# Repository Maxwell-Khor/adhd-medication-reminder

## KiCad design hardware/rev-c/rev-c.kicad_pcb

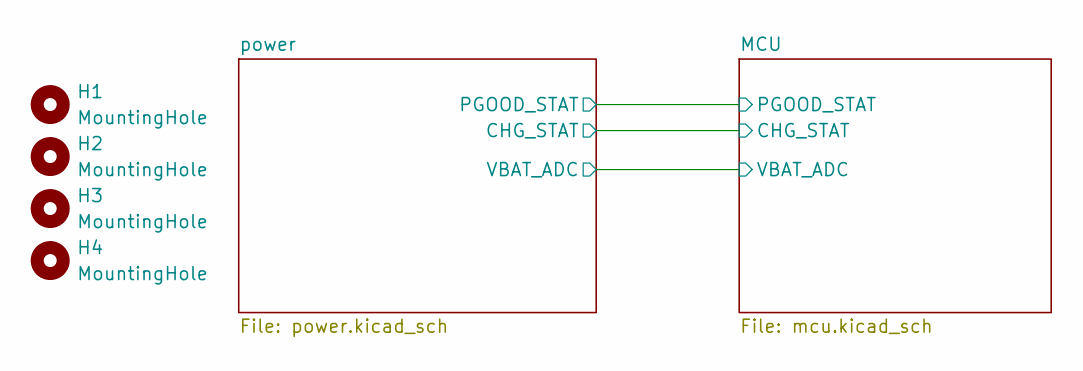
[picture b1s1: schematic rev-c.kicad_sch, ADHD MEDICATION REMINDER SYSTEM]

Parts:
H1, H2, H3, H4: MountingHole; MountingHole_2.2mm_M2_Pad

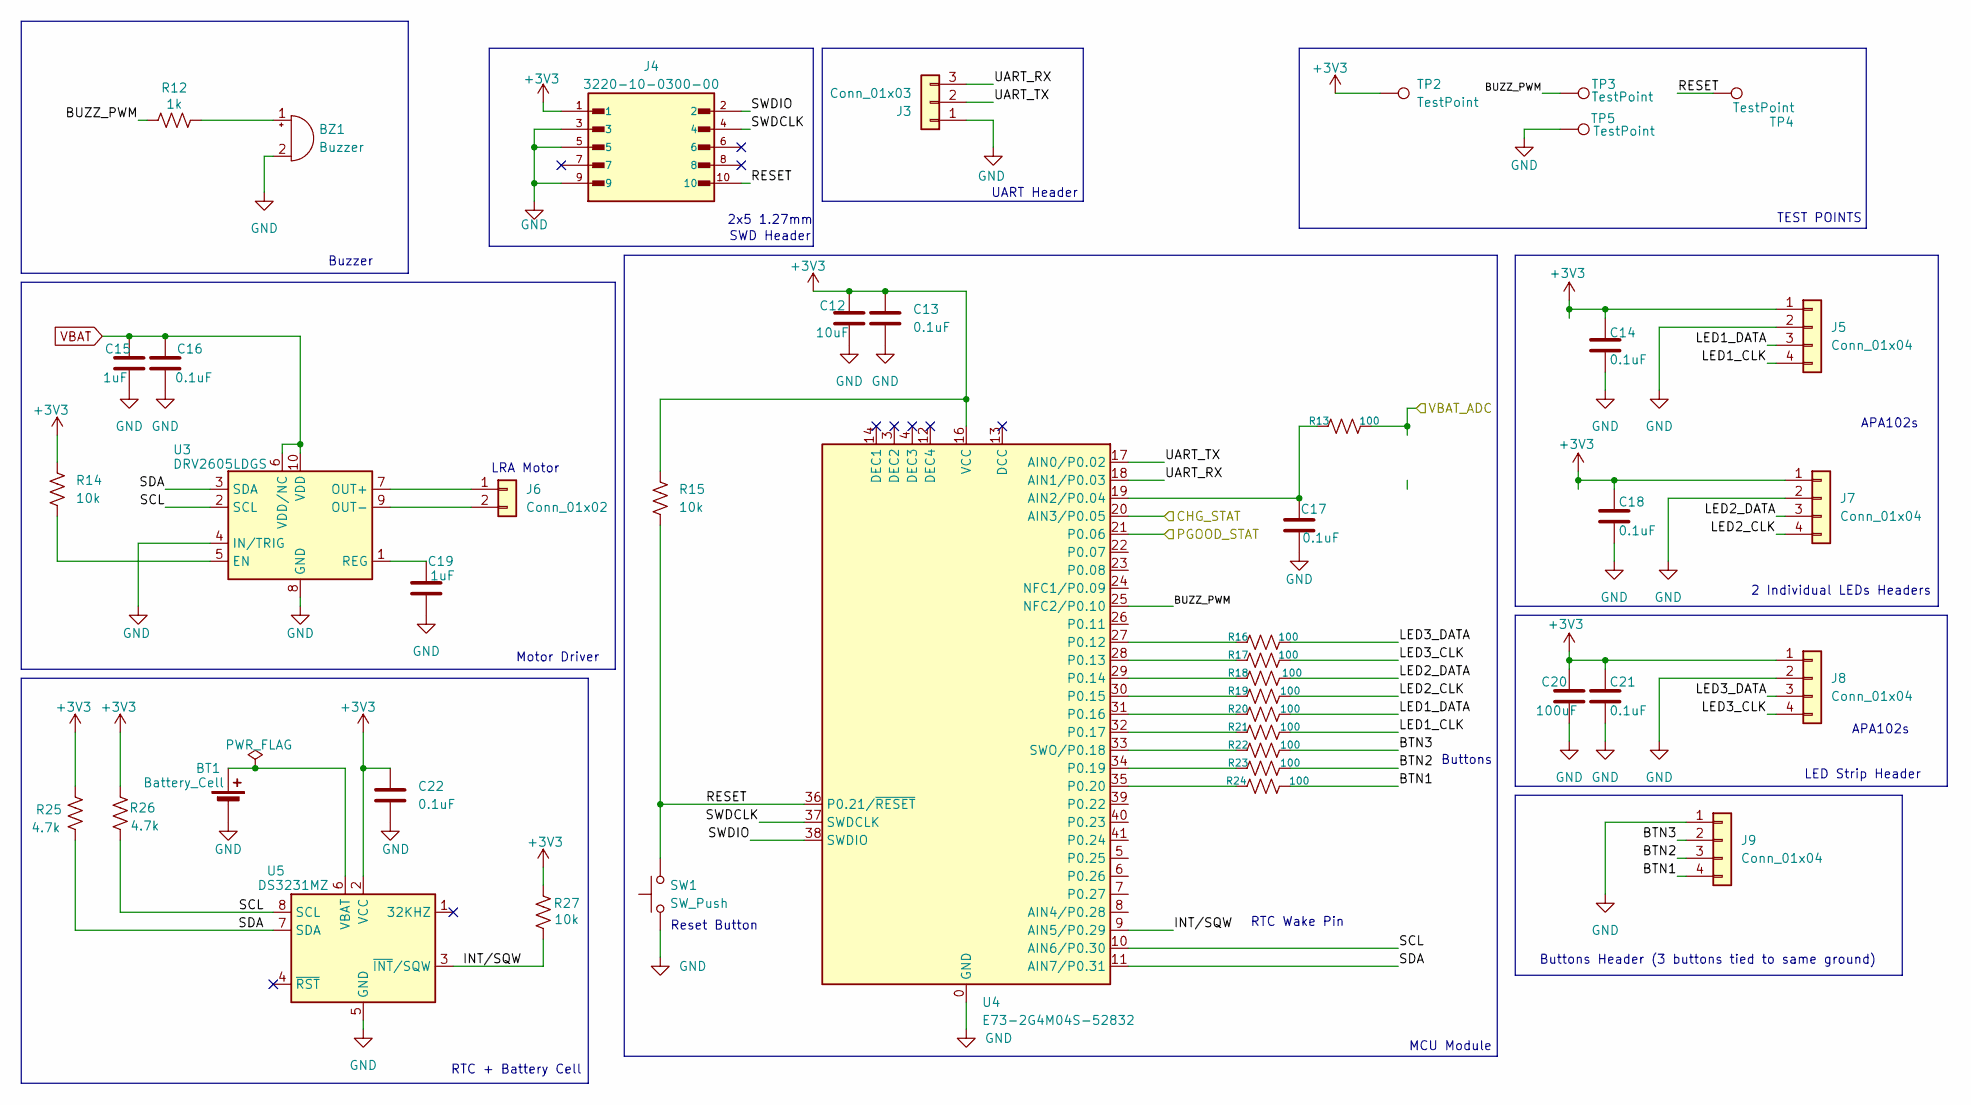
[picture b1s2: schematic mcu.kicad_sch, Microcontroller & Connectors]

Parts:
BT1: Battery_Cell; BatteryHolder_Keystone_3034_1x20mm
BZ1: Buzzer; XDCR_PS1240P02BT
C12: 10uF; C_0603_1608Metric
C13, C14, C16, C17, C18, C21, C22: 0.1uF; C_0603_1608Metric
C15, C19: 1uF; C_0603_1608Metric
C20: 100uF; CP_Elec_5x5.4
J3: Conn_01x03; PinHeader_1x03_P2.54mm_Vertical
J4: 3220-10-0300-00; PinHeader_2x05_P1.27mm_Vertical; PARTREV D
J5, J7, J8, J9: Conn_01x04; JST_PH_B4B-PH-K_1x04_P2.00mm_Vertical
J6: Conn_01x02; JST_PH_B2B-PH-K_1x02_P2.00mm_Vertical
R12: 1k; R_0603_1608Metric
R13, R16, R17, R18, R19, R20, R21, R22, R23, R24: 100; R_0603_1608Metric
R14, R15, R27: 10k; R_0603_1608Metric
R25, R26: 4.7k; R_0603_1608Metric
SW1: SW_Push; SW_SPST_SKQG_WithStem
TP2, TP3, TP4, TP5: TestPoint; TestPoint_Pad_D1.5mm
U3: DRV2605LDGS; VSSOP-10_3x3mm_P0.5mm
U4: E73-2G4M04S-52832; E73-2G4M04S
U5: DS3231MZ; SOIC-8_3.9x4.9mm_P1.27mm

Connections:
+3V3: C12.1, C13.1, C14.1, C18.1, C20.1, C21.1, C22.1, J4.1, J5.1, J7.1, J8.1, R14.1, R15.1, R25.2, R26.2, R27.2, TP2.1, U4.16 (VCC), U5.2 (VCC); also elsewhere on the board
/MCU/BTN1: J9.4, R24.1
/MCU/BTN2: J9.3, R23.1
/MCU/BTN3: J9.2, R22.1
/MCU/BUZZ_PWM: R12.1, TP3.1, U4.25 (NFC2/P0.10)
/MCU/CHG_STAT: U4.20 (AIN3/P0.05); also elsewhere on the board
/MCU/INT/SQW: R27.1, U4.9 (AIN5/P0.29), U5.3 (~INT/SQW)
/MCU/LED1_CLK: J5.4, R21.1
/MCU/LED1_DATA: J5.3, R20.1
/MCU/LED2_CLK: J7.4, R19.1
/MCU/LED2_DATA: J7.3, R18.2
/MCU/LED3_CLK: J8.4, R17.2
/MCU/LED3_DATA: J8.3, R16.2
/MCU/PGOOD_STAT: U4.21 (P0.06); also elsewhere on the board
/MCU/RESET: J4.10, R15.2, SW1.2, TP4.1, U4.36 (P0.21/~RESET)
/MCU/SCL: R26.1, U3.2 (SCL), U4.10 (AIN6/P0.30), U5.8 (SCL)
/MCU/SDA: R25.1, U3.3 (SDA), U4.11 (AIN7/P0.31), U5.7 (SDA)
/MCU/SWDCLK: J4.4, U4.37 (SWDCLK)
/MCU/SWDIO: J4.2, U4.38 (SWDIO)
/MCU/UART_RX: J3.3, U4.18 (AIN1/P0.03)
/MCU/UART_TX: J3.2, U4.17 (AIN0/P0.02)
/MCU/VBAT_ADC: R13.2; also elsewhere on the board
GND: BT1.2 (-), BZ1.2 (-), C12.2, C13.2, C14.2, C15.2, C16.2, C17.1, C18.2, C19.2, C20.2, C21.2, C22.2, J3.1, J4.3, J4.5, J4.9, J5.2, J7.2, J8.2, J9.1, SW1.1, TP5.1, U3.4 (IN/TRIG), U3.8 (GND), U4.0 (GND), U4.1 (GND), U4.2 (GND), U4.15 (GND), U4.42 (GND), U4.43 (GND), U5.5 (GND); also elsewhere on the board
unnamed: BT1.1 (+), U5.6 (VBAT)
unnamed: BZ1.1 (+), R12.2
unnamed: J6.1, U3.7 (OUT+)
unnamed: J6.2, U3.9 (OUT-)
unnamed: R14.2, U3.5 (EN)
unnamed: C19.1, U3.1 (REG)
unnamed: C17.2, R13.1, U4.19 (AIN2/P0.04)
unnamed: R16.1, U4.27 (P0.12)
unnamed: R17.1, U4.28 (P0.13)
unnamed: R18.1, U4.29 (P0.14)
unnamed: R19.2, U4.30 (P0.15)
unnamed: R20.2, U4.31 (P0.16)
unnamed: R21.2, U4.32 (P0.17)
unnamed: R23.2, U4.34 (P0.19)
unnamed: R24.2, U4.35 (P0.20)
unnamed: R22.2, U4.33 (SWO/P0.18)
VBAT: C15.1, C16.1, U3.6 (VDD/NC), U3.10 (VDD); also elsewhere on the board

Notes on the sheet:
LED Strip Header
MCU Module
RTC Wake Pin
RTC + Battery Cell
LRA Motor
Motor Driver
APA102s
Reset Button
UART Header
SWD Header
Buttons Header (3 buttons tied to same ground)
Buzzer
Buttons
TEST POINTS
2x5 1.27mm
2 Individual LEDs Headers

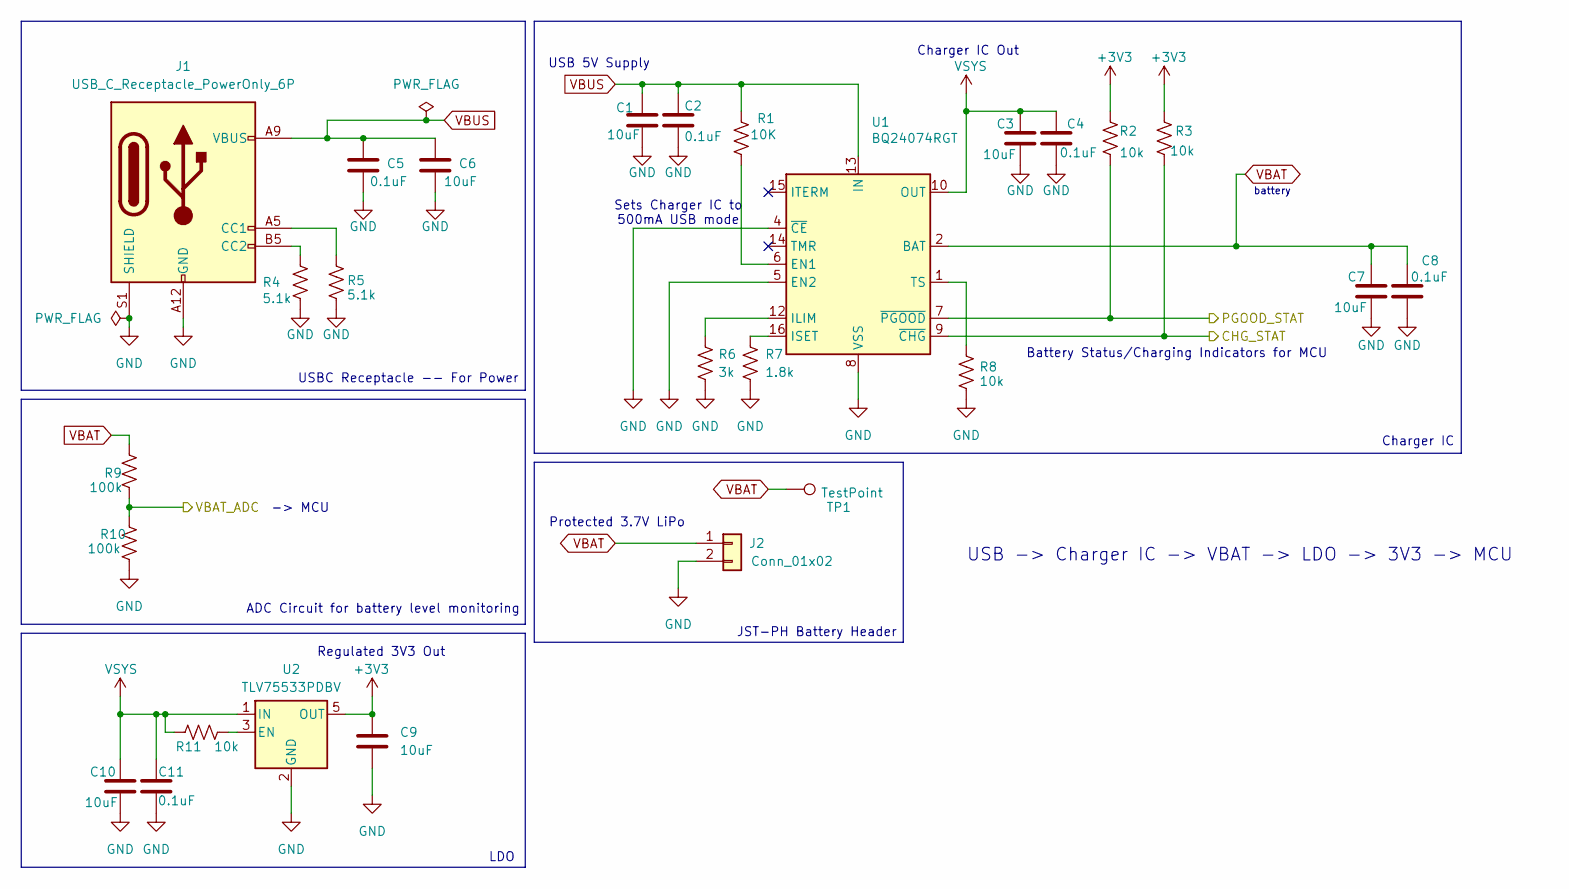
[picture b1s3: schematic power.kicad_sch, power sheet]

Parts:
C1, C3, C6, C7, C9, C10: 10uF; C_0603_1608Metric
C2, C4, C5, C8, C11: 0.1uF; C_0603_1608Metric
J1: USB_C_Receptacle_PowerOnly_6P; USB_C_Receptacle_HRO_TYPE-C-31-M-17
J2: Conn_01x02; JST_PH_B2B-PH-K_1x02_P2.00mm_Vertical
R1: 10K; R_0603_1608Metric
R2, R3, R8, R11: 10k; R_0603_1608Metric
R4, R5: 5.1k; R_0603_1608Metric
R6: 3k; R_0603_1608Metric
R7: 1.8k; R_0603_1608Metric
R9, R10: 100k; R_0603_1608Metric
TP1: TestPoint; TestPoint_Pad_D1.5mm
U1: BQ24074RGT; QFN-16-1EP_3x3mm_P0.5mm_EP1.7x1.7mm_ThermalVias
U2: TLV75533PDBV; SOT-23-5

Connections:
+3V3: C9.1, R2.2, R3.1, U2.5 (OUT); also elsewhere on the board
/MCU/CHG_STAT: R3.2, U1.9 (~CHG); also elsewhere on the board
/MCU/PGOOD_STAT: R2.1, U1.7 (~PGOOD); also elsewhere on the board
/MCU/VBAT_ADC: R9.1, R10.2; also elsewhere on the board
GND: C1.1, C2.1, C3.1, C4.1, C5.2, C6.2, C7.1, C8.1, C9.2, C10.1, C11.1, J1.A12 (GND), J1.B12 (GND), J1.S1 (SHIELD), J2.2, R4.2, R5.1, R6.2, R7.2, R8.2, R10.1, U1.4 (~CE), U1.5 (EN2), U1.8 (VSS), U1.17 (VSS), U2.2 (GND); also elsewhere on the board
unnamed: J1.A5 (CC1), R5.2
unnamed: J1.B5 (CC2), R4.1
unnamed: R1.1, U1.6 (EN1)
unnamed: R6.1, U1.12 (ILIM)
unnamed: R7.1, U1.16 (ISET)
unnamed: R8.1, U1.1 (TS)
unnamed: R11.2, U2.3 (EN)
VBAT: C7.2, C8.2, J2.1, R9.2, TP1.1, U1.2 (BAT), U1.3 (BAT); also elsewhere on the board
VBUS: C1.2, C2.2, C5.1, C6.1, J1.A9 (VBUS), J1.B9 (VBUS), R1.2, U1.13 (IN)
VSYS: C3.2, C4.2, C10.2, C11.2, R11.1, U1.10 (OUT), U1.11 (OUT), U2.1 (IN)

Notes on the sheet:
USBC Receptacle -- For Power
Protected 3.7V LiPo
Battery Status/Charging Indicators for MCU
JST-PH Battery Header
ADC Circuit for battery level monitoring
battery
Regulated 3V3 Out
USB -> Charger IC -> VBAT -> LDO -> 3V3 -> MCU
-> MCU
Sets Charger IC to 500mA USB mode
Charger IC
LDO
Charger IC Out
USB 5V Supply

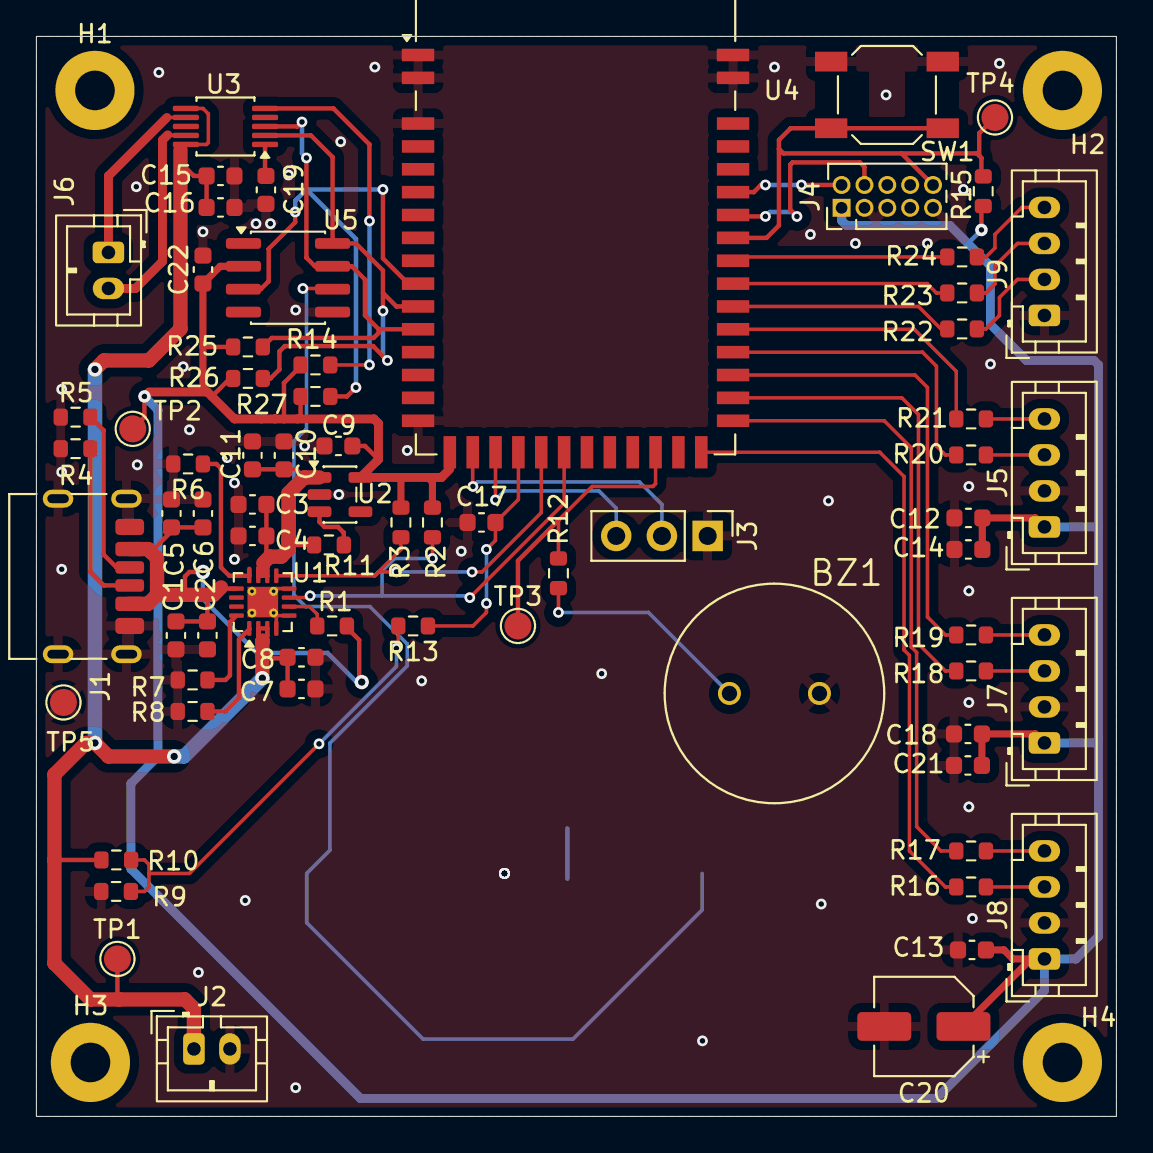
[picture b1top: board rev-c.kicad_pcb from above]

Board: 2 copper layers, 60.0 x 60.0 mm, 75 parts (1 on the bottom side), 49 nets.

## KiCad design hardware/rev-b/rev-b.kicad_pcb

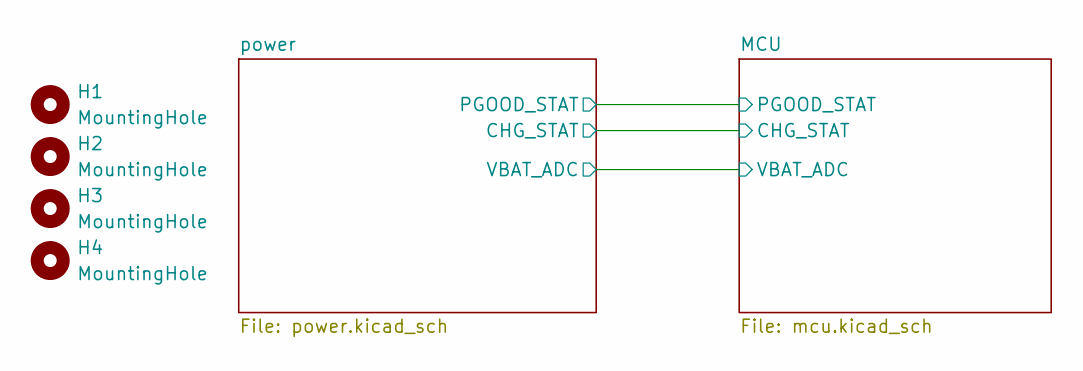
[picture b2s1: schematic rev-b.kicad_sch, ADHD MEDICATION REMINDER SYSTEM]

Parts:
H1, H2, H3, H4: MountingHole; MountingHole_2.2mm_M2_Pad

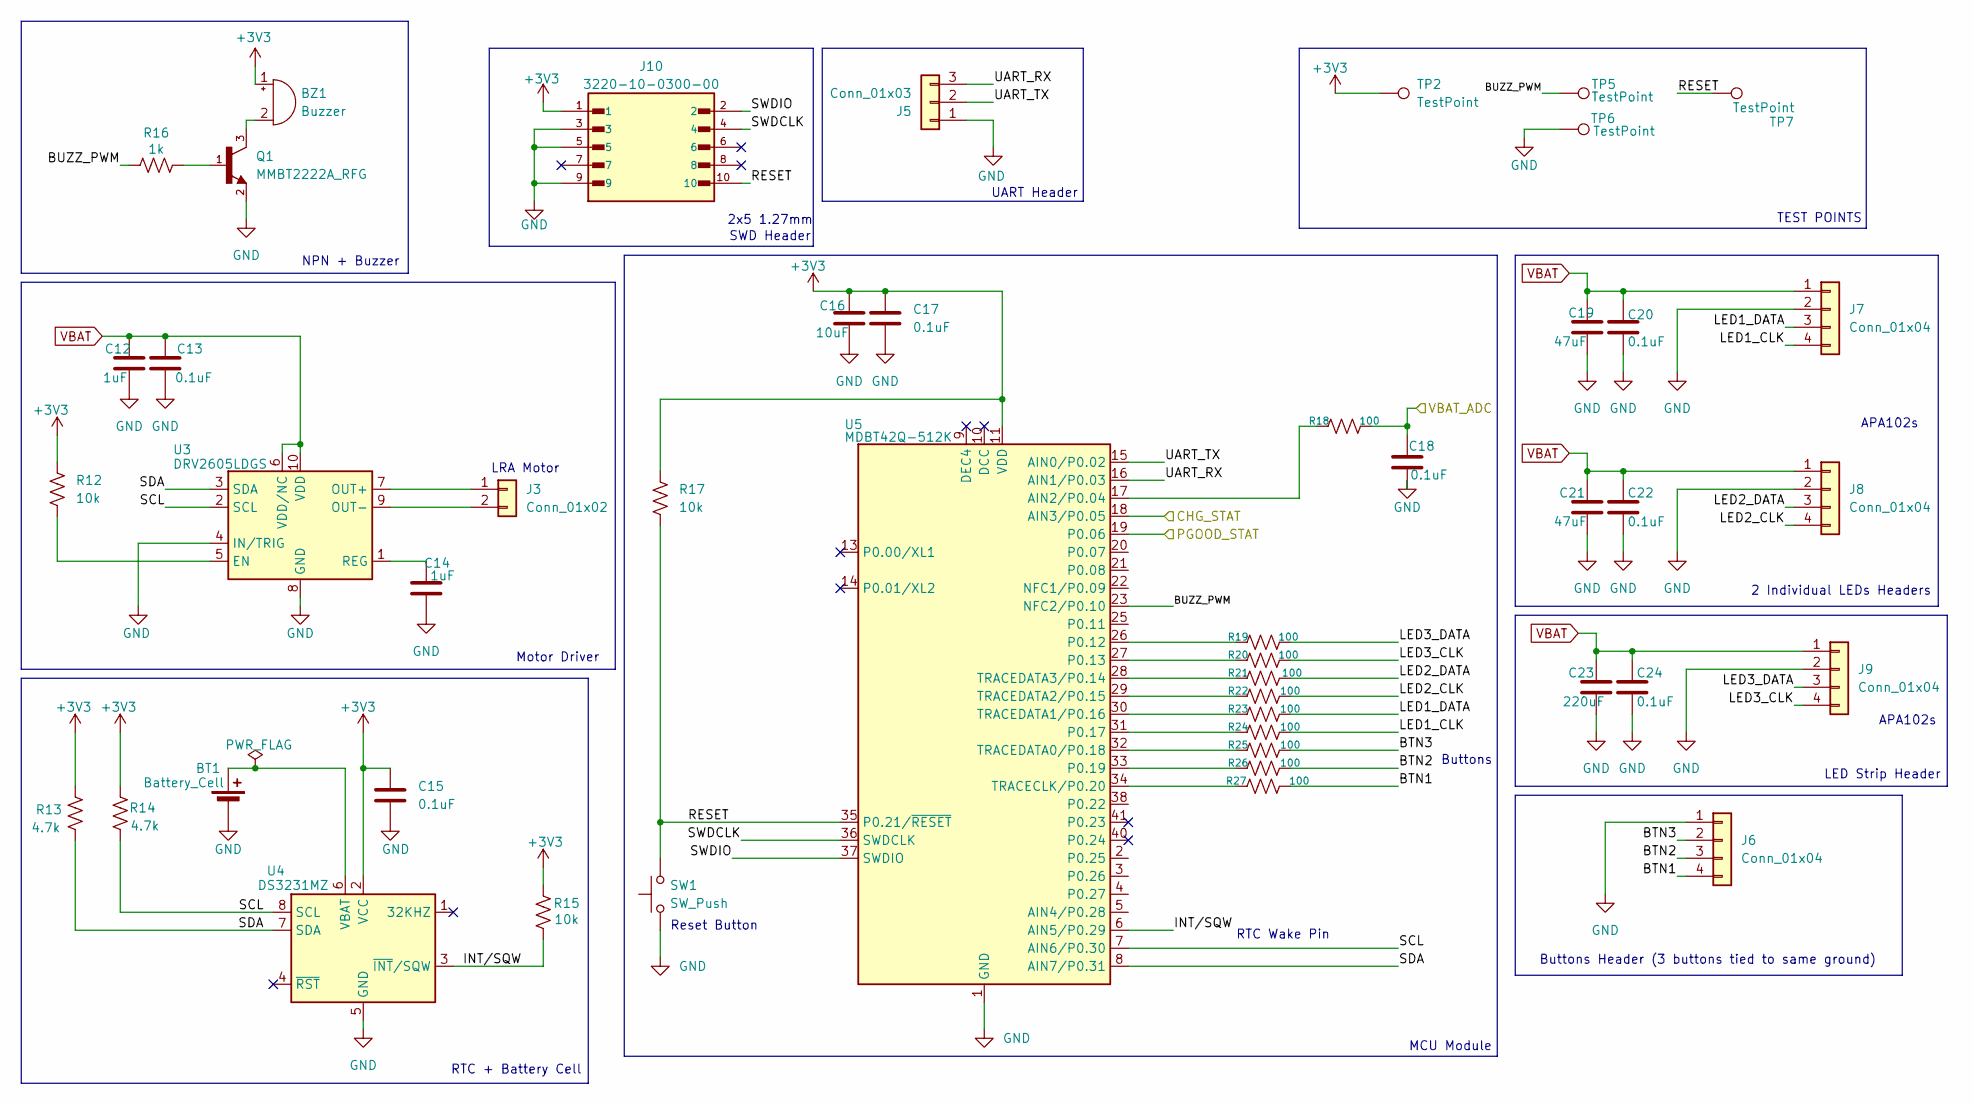
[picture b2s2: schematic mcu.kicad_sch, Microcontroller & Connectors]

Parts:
BT1: Battery_Cell; BatteryHolder_Keystone_3034_1x20mm
BZ1: Buzzer; CUI_CMT-1203-SMT
C12, C14: 1uF; C_0603_1608Metric
C13, C15, C17, C18, C20, C22, C24: 0.1uF; C_0603_1608Metric
C16: 10uF; C_0603_1608Metric
C19, C21: 47uF; C_0603_1608Metric
C23: 220uF; CP_Elec_5x5.3
J3: Conn_01x02; JST_PH_B2B-PH-K_1x02_P2.00mm_Vertical
J5: Conn_01x03; PinHeader_1x03_P2.54mm_Vertical
J6, J7, J8, J9: Conn_01x04; JST_PH_B4B-PH-K_1x04_P2.00mm_Vertical
J10: 3220-10-0300-00; PinHeader_2x05_P1.27mm_Vertical; PARTREV D
Q1: MMBT2222A_RFG; SOT-23; PARTREV I2001
R12, R15, R17: 10k; R_0603_1608Metric
R13, R14: 4.7k; R_0603_1608Metric
R16: 1k; R_0603_1608Metric
R18, R19, R20, R21, R22, R23, R24, R25, R26, R27: 100; R_0603_1608Metric
SW1: SW_Push; SW_SPST_EVQP0
TP2, TP5, TP6, TP7: TestPoint; TestPoint_Pad_D1.5mm
U3: DRV2605LDGS; VSSOP-10_3x3mm_P0.5mm
U4: DS3231MZ; SOIC-8_3.9x4.9mm_P1.27mm
U5: MDBT42Q-512K; Raytac_MDBT42Q

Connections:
+3V3: BZ1.1 (+), C15.1, C16.1, C17.1, J10.1, R12.1, R13.2, R14.2, R15.2, R17.1, TP2.1, U4.2 (VCC), U5.11 (VDD); also elsewhere on the board
/MCU/BTN1: J6.4, R27.1
/MCU/BTN2: J6.3, R26.1
/MCU/BTN3: J6.2, R25.1
/MCU/BUZZ_PWM: R16.1, TP5.1, U5.23 (NFC2/P0.10)
/MCU/CHG_STAT: U5.18 (AIN3/P0.05); also elsewhere on the board
/MCU/INT/SQW: R15.1, U4.3 (~INT/SQW), U5.6 (AIN5/P0.29)
/MCU/LED1_CLK: J7.4, R24.1
/MCU/LED1_DATA: J7.3, R23.1
/MCU/LED2_CLK: J8.4, R22.1
/MCU/LED2_DATA: J8.3, R21.2
/MCU/LED3_CLK: J9.4, R20.2
/MCU/LED3_DATA: J9.3, R19.2
/MCU/PGOOD_STAT: U5.19 (P0.06); also elsewhere on the board
/MCU/RESET: J10.10, R17.2, SW1.2, TP7.1, U5.35 (P0.21/~RESET)
/MCU/SCL: R14.1, U3.2 (SCL), U4.8 (SCL), U5.7 (AIN6/P0.30)
/MCU/SDA: R13.1, U3.3 (SDA), U4.7 (SDA), U5.8 (AIN7/P0.31)
/MCU/SWDCLK: J10.4, U5.36 (SWDCLK)
/MCU/SWDIO: J10.2, U5.37 (SWDIO)
/MCU/UART_RX: J5.3, U5.16 (AIN1/P0.03)
/MCU/UART_TX: J5.2, U5.15 (AIN0/P0.02)
/MCU/VBAT_ADC: C18.2, R18.2; also elsewhere on the board
GND: BT1.2 (-), C12.2, C13.2, C14.2, C15.2, C16.2, C17.2, C18.1, C19.2, C20.2, C21.2, C22.2, C23.2, C24.2, J5.1, J6.1, J7.2, J8.2, J9.2, J10.3, J10.5, J10.9, Q1.2, SW1.1, TP6.1, U3.4 (IN/TRIG), U3.8 (GND), U4.5 (GND), U5.1 (GND), U5.12 (GND), U5.24 (GND), U5.39 (GND); also elsewhere on the board
unnamed: BT1.1 (+), U4.6 (VBAT)
unnamed: BZ1.2 (-), Q1.3
unnamed: J3.1, U3.7 (OUT+)
unnamed: J3.2, U3.9 (OUT-)
unnamed: Q1.1, R16.2
unnamed: R12.2, U3.5 (EN)
unnamed: C14.1, U3.1 (REG)
unnamed: R18.1, U5.17 (AIN2/P0.04)
unnamed: R19.1, U5.26 (P0.12)
unnamed: R20.1, U5.27 (P0.13)
unnamed: R24.2, U5.31 (P0.17)
unnamed: R26.2, U5.33 (P0.19)
unnamed: R27.2, U5.34 (TRACECLK/P0.20)
unnamed: R25.2, U5.32 (TRACEDATA0/P0.18)
unnamed: R23.2, U5.30 (TRACEDATA1/P0.16)
unnamed: R22.2, U5.29 (TRACEDATA2/P0.15)
unnamed: R21.1, U5.28 (TRACEDATA3/P0.14)
VBAT: C12.1, C13.1, C19.1, C20.1, C21.1, C22.1, C23.1, C24.1, J7.1, J8.1, J9.1, U3.6 (VDD/NC), U3.10 (VDD); also elsewhere on the board

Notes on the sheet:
LED Strip Header
MCU Module
RTC Wake Pin
RTC + Battery Cell
LRA Motor
Motor Driver
APA102s
Reset Button
UART Header
SWD Header
Buttons Header (3 buttons tied to same ground)
NPN + Buzzer
Buttons
TEST POINTS
2x5 1.27mm
2 Individual LEDs Headers

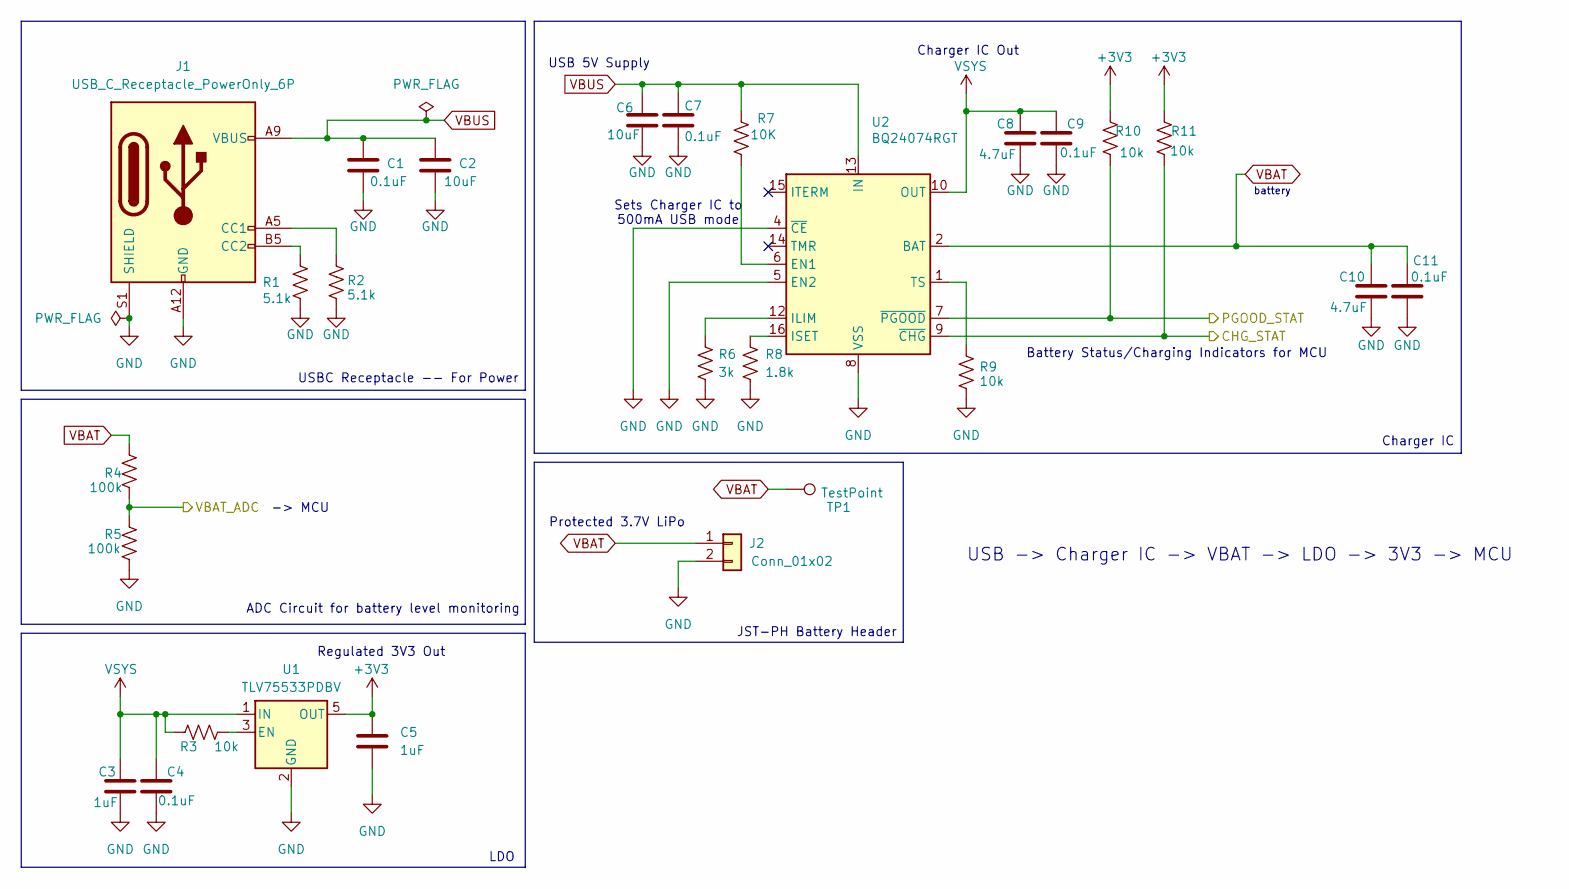
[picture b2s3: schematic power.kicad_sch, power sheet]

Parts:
C1, C4, C7, C9, C11: 0.1uF; C_0603_1608Metric
C2, C6: 10uF; C_0603_1608Metric
C3, C5: 1uF; C_0603_1608Metric
C8, C10: 4.7uF; C_0603_1608Metric
J1: USB_C_Receptacle_PowerOnly_6P; GCT_USB4125-GF-A_REVA2
J2: Conn_01x02; JST_PH_B2B-PH-K_1x02_P2.00mm_Vertical
R1, R2: 5.1k; R_0603_1608Metric
R3, R9, R10, R11: 10k; R_0603_1608Metric
R4, R5: 100k; R_0603_1608Metric
R6: 3k; R_0603_1608Metric
R7: 10K; R_0603_1608Metric
R8: 1.8k; R_0603_1608Metric
TP1: TestPoint; TestPoint_Pad_D1.5mm
U1: TLV75533PDBV; SOT-23-5
U2: BQ24074RGT; QFN-16-1EP_3x3mm_P0.5mm_EP1.7x1.7mm_ThermalVias

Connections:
+3V3: C5.1, R10.2, R11.1, U1.5 (OUT); also elsewhere on the board
/MCU/CHG_STAT: R11.2, U2.9 (~CHG); also elsewhere on the board
/MCU/PGOOD_STAT: R10.1, U2.7 (~PGOOD); also elsewhere on the board
/MCU/VBAT_ADC: R4.1, R5.2; also elsewhere on the board
GND: C1.2, C2.2, C3.1, C4.1, C5.2, C6.1, C7.1, C8.1, C9.1, C10.1, C11.1, J1.A12 (GND), J1.B12 (GND), J1.S1 (SHIELD), J2.2, R1.2, R2.1, R5.1, R6.2, R8.2, R9.2, U1.2 (GND), U2.4 (~CE), U2.5 (EN2), U2.8 (VSS), U2.17 (VSS); also elsewhere on the board
unnamed: J1.A5 (CC1), R2.2
unnamed: J1.B5 (CC2), R1.1
unnamed: R3.2, U1.3 (EN)
unnamed: R7.1, U2.6 (EN1)
unnamed: R6.1, U2.12 (ILIM)
unnamed: R8.1, U2.16 (ISET)
unnamed: R9.1, U2.1 (TS)
VBAT: C10.2, C11.2, J2.1, R4.2, TP1.1, U2.2 (BAT), U2.3 (BAT); also elsewhere on the board
VBUS: C1.1, C2.1, C6.2, C7.2, J1.A9 (VBUS), J1.B9 (VBUS), R7.2, U2.13 (IN)
VSYS: C3.2, C4.2, C8.2, C9.2, R3.1, U1.1 (IN), U2.10 (OUT), U2.11 (OUT)

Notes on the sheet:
USBC Receptacle -- For Power
Protected 3.7V LiPo
Battery Status/Charging Indicators for MCU
JST-PH Battery Header
ADC Circuit for battery level monitoring
battery
Regulated 3V3 Out
USB -> Charger IC -> VBAT -> LDO -> 3V3 -> MCU
-> MCU
Sets Charger IC to 500mA USB mode
Charger IC
LDO
Charger IC Out
USB 5V Supply

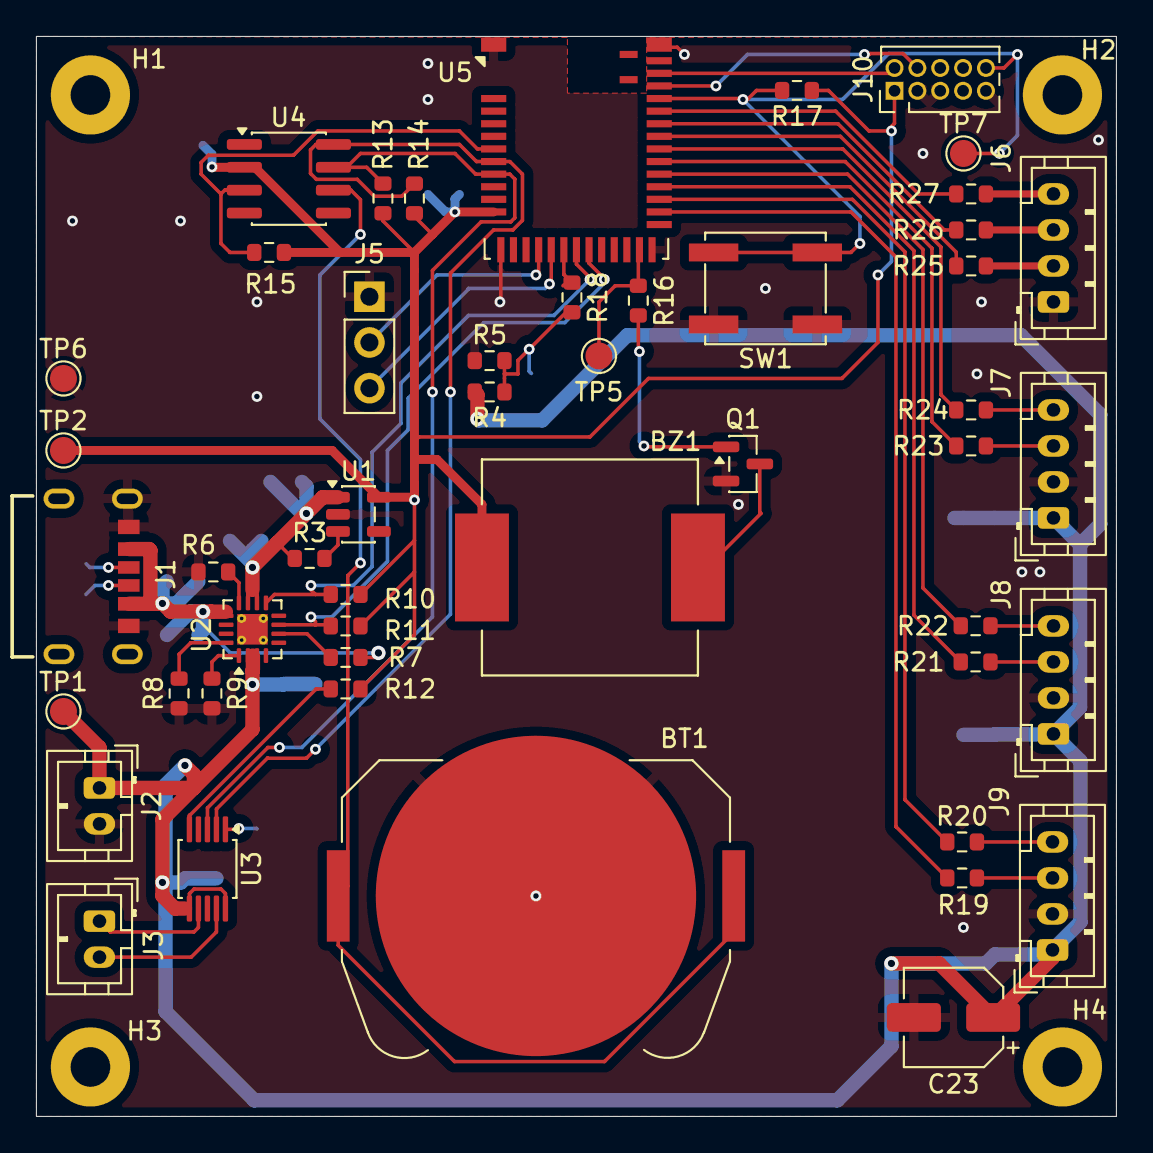
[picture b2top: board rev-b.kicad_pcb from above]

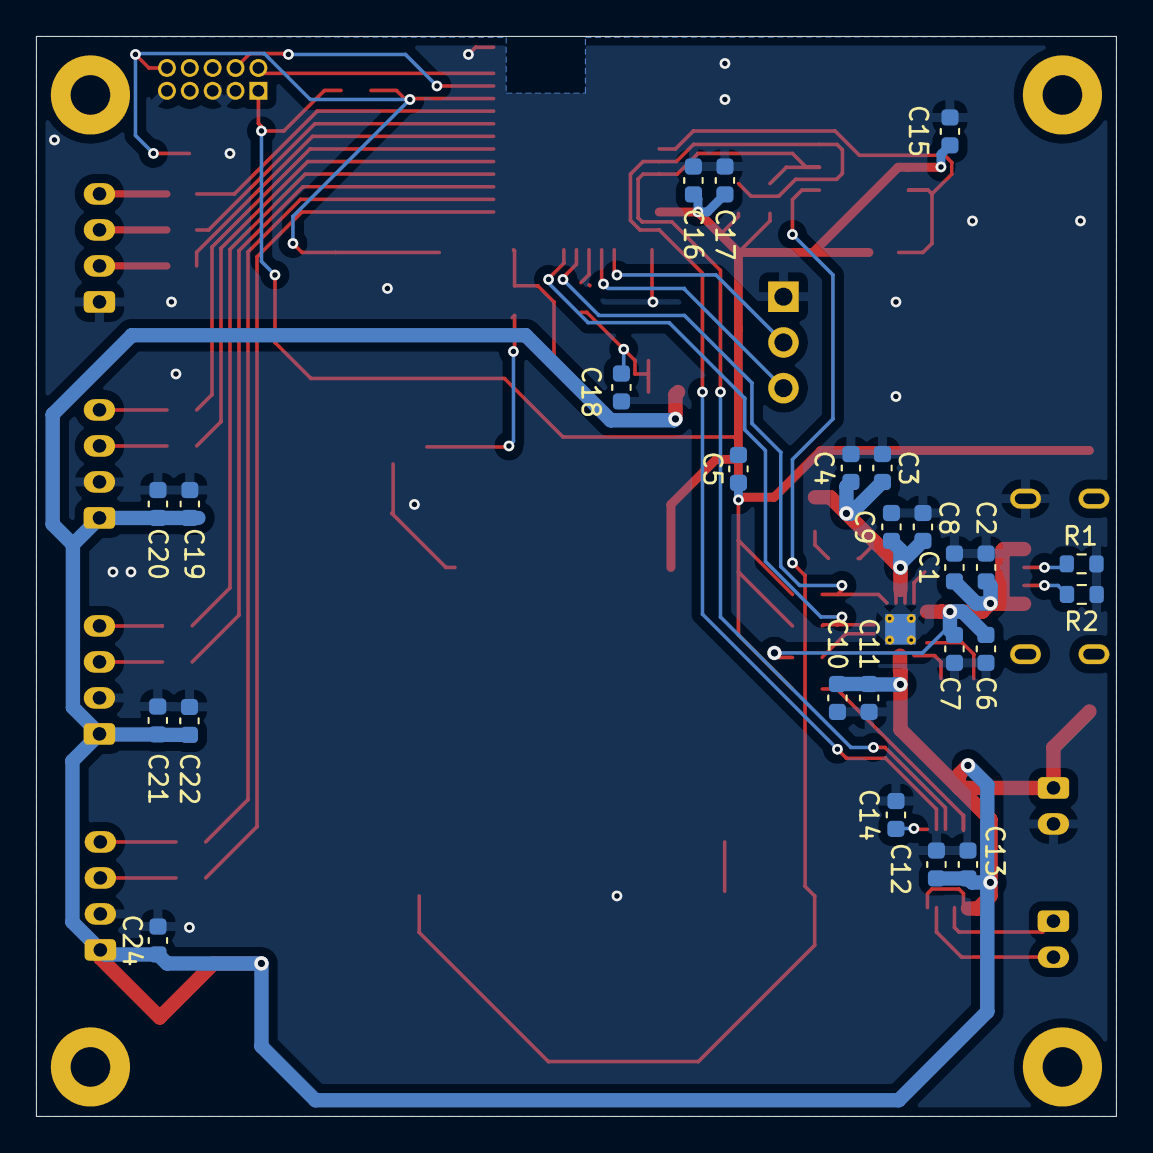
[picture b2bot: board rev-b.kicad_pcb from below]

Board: 2 copper layers, 60.0 x 60.0 mm, 78 parts (25 on the bottom side), 50 nets.

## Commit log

2026-03-10 Add ADHD PCB V1 hardware project
2026-03-10 Removed DS_Store system files
2026-03-10 Update gitignore to ignore DS_Store
2026-03-10 Clean repository and remove DS_Store files
2026-03-10 Add firmware and documentation folder structure
2026-03-10 Add firmware and documentation placeholders
2026-03-10 Rename hardware revision to rev-a
2026-03-11 Create power and MCU hierarchal pages
2026-03-13 finalize MCU sheet and add haptic feedback sheet
2026-03-13 Annotate schematic hierarchy and fix LED routing
2026-03-13 rev: schematic revision B
2026-03-15 intialize PCB layout document
2026-03-18 Assign footprints and add additional bypass caps
2026-03-18 updated layout from schematic
2026-03-20 format schematic to fit convention, replace SWD header with 2x5
2026-03-20 rev c with labeled ICs
2026-03-22 crackhead layout file added
2026-03-23 Add files via upload
    Datasheets
2026-03-23 plot fab and assembly files
2026-03-25 rev c layout complete
